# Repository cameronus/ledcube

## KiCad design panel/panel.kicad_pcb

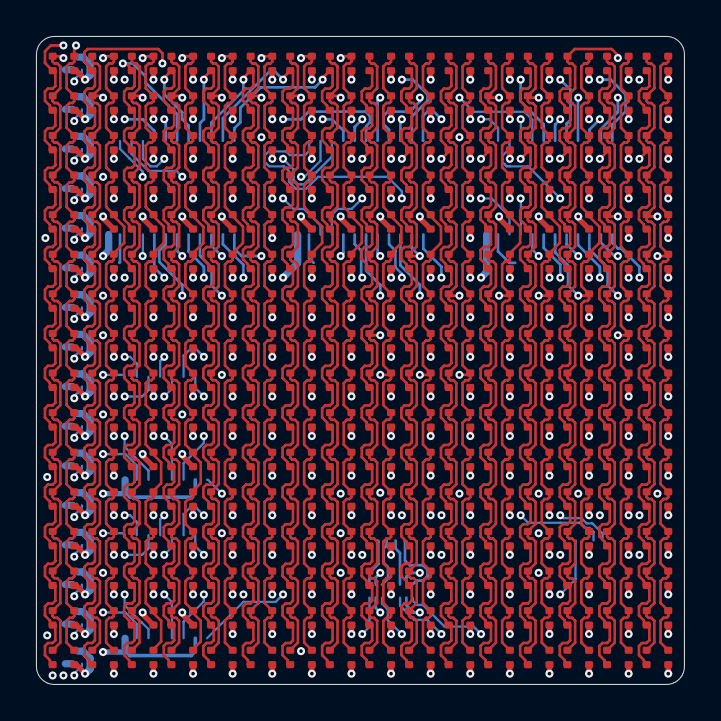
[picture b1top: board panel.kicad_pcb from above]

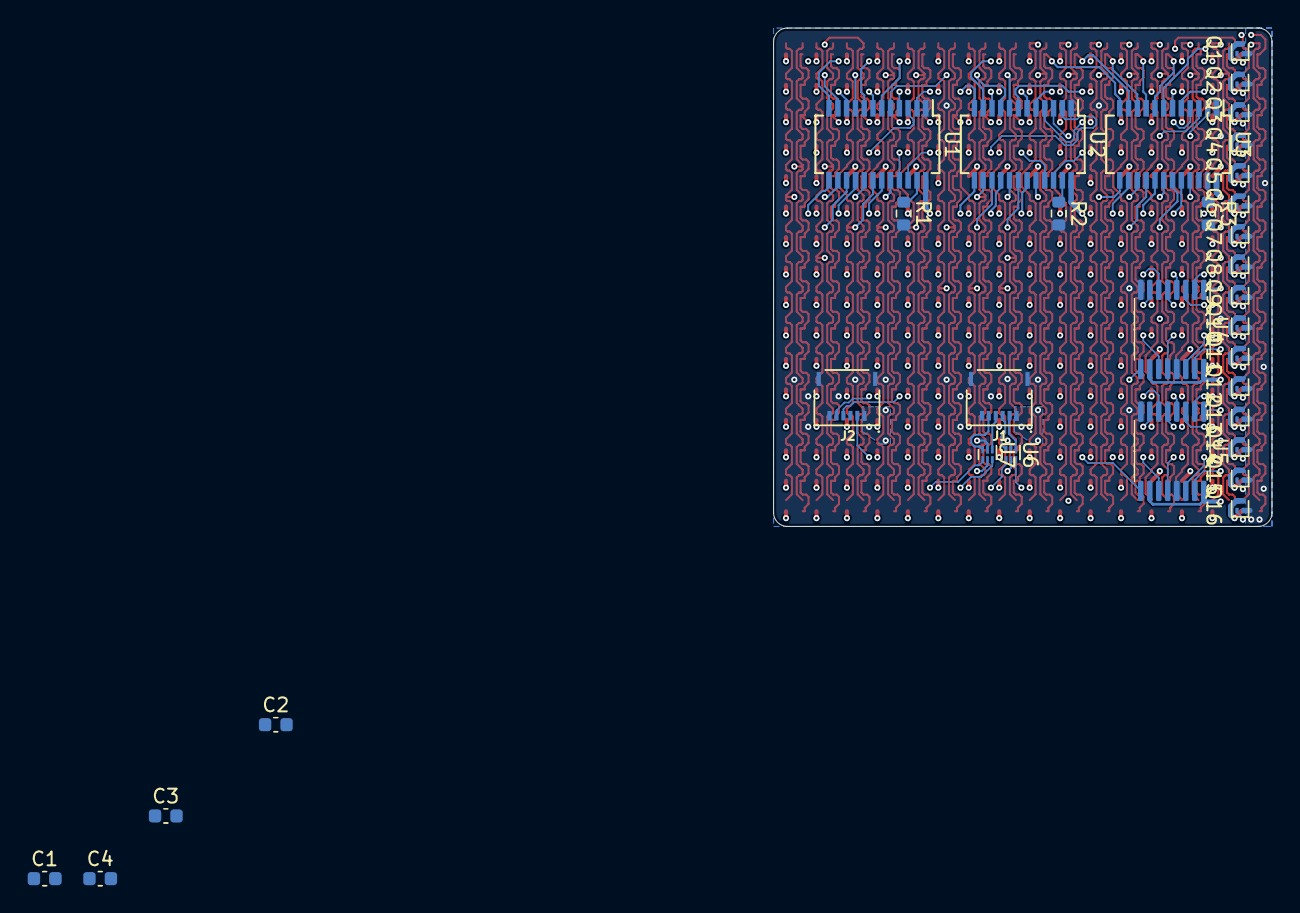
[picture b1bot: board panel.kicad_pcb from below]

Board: 4 copper layers, 36.0 x 36.0 mm, 288 parts (32 on the bottom side), 98 nets.

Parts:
C1, C2, C3, C4: 0.1uF; C_0603_1608Metric
D1, D2, D3, D4, D5, D6, D7, D8, D9, D10, D11, D12, D13, D14, D15, D16, D17, D18, D19, D20, D21, D22, D23, D24, D25, D26, D27, D28, D29, D30, D31, D32, D33, D34, D35, D36, D37, D38, D39, D40, D41, D42, D43, D44, D45, D46, D47, D48, D49, D50, D51, D52, D53, D54, D55, D56, D57, D58, D59, D60, D61, D62, D63, D64, D65, D66, D67, D68, D69, D70, D71, D72, D73, D74, D75, D76, D77, D78, D79, D80, D81, D82, D83, D84, D85, D86, D87, D88, D89, D90, D91, D92, D93, D94, D95, D96, D97, D98, D99, D100, D101, D102, D103, D104, D105, D106, D107, D108, D109, D110, D111, D112, D113, D114, D115, D116, D117, D118, D119, D120, D121, D122, D123, D124, D125, D126, D127, D128, D129, D130, D131, D132, D133, D134, D135, D136, D137, D138, D139, D140, D141, D142, D143, D144, D145, D146, D147, D148, D149, D150, D151, D152, D153, D154, D155, D156, D157, D158, D159, D160, D161, D162, D163, D164, D165, D166, D167, D168, D169, D170, D171, D172, D173, D174, D175, D176, D177, D178, D179, D180, D181, D182, D183, D184, D185, D186, D187, D188, D189, D190, D191, D192, D193, D194, D195, D196, D197, D198, D199, D200, D201, D202, D203, D204, D205, D206, D207, D208, D209, D210, D211, D212, D213, D214, D215, D216, D217, D218, D219, D220, D221, D222, D223, D224, D225, D226, D227, D228, D229, D230, D231, D232, D233, D234, D235, D236, D237, D238, D239, D240, D241, D242, D243, D244, D245, D246, D247, D248, D249, D250, D251, D252, D253, D254, D255, D256: LED_RABG; MHPA1515RGBDT
J1: IN; 5034800600
J2: OUT; 5034800600
Q1, Q2, Q3, Q4, Q5, Q6, Q7, Q8, Q9, Q10, Q11, Q12, Q13, Q14, Q15, Q16: Q_PMOS_GSD; SOT-883
R1: 2.2k; R_0603_1608Metric
R2: 7.5k; R_0603_1608Metric
R3: 4.12k; R_0603_1608Metric
U1, U2, U3: TLC59025; SSOP-24_3.9x8.7mm_P0.635mm
U4, U5: SN74HC595; TSSOP-16_4.4x5mm_P0.65mm
U6, U7: NC7WZ17; Fairchild_MicroPak2-6_1.0x1.0mm_P0.35mm

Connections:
/BLANK: J2.5, U1.21 (~OE), U2.21 (~OE), U3.21 (~OE), U7.4 (Y2)
/BLANK_IN: J1.5, U7.3 (A2)
/CLK: J2.2, U1.3 (CLK), U2.3 (CLK), U3.3 (CLK), U4.11 (SRCLK), U5.11 (SRCLK), U6.6 (Y1)
/CLK_IN: J1.2, U6.1 (A1)
/DAT: U4.14 (SER), U6.4 (Y2)
/DAT2: U4.9 (QH'), U5.14 (SER)
/DAT3: U1.2 (SDI), U5.9 (QH')
/DAT4: U1.22 (SDO), U2.2 (SDI)
/DAT5: U2.22 (SDO), U3.2 (SDI)
/DAT_IN: J1.3, U6.3 (A2)
/DAT_OUT: J2.3, U3.22 (SDO)
/LATCH: J2.4, U1.4 (LE), U2.4 (LE), U3.4 (LE), U4.12 (RCLK), U5.12 (RCLK), U7.6 (Y1)
/LATCH_IN: J1.4, U7.1 (A1)
/ROW_0: Q1.1 (G), U4.15 (QA)
/ROW_0/COMMON: D1.2 (A), D2.2 (A), D3.2 (A), D4.2 (A), D5.2 (A), D6.2 (A), D7.2 (A), D8.2 (A), D9.2 (A), D10.2 (A), D11.2 (A), D12.2 (A), D13.2 (A), D14.2 (A), D15.2 (A), D16.2 (A), Q1.3 (D)
/ROW_1: Q2.1 (G), U4.1 (QB)
/ROW_1/COMMON: D17.2 (A), D18.2 (A), D19.2 (A), D20.2 (A), D21.2 (A), D22.2 (A), D23.2 (A), D24.2 (A), D25.2 (A), D26.2 (A), D27.2 (A), D28.2 (A), D29.2 (A), D30.2 (A), D31.2 (A), D32.2 (A), Q2.3 (D)
/ROW_2: Q3.1 (G), U4.2 (QC)
/ROW_2/COMMON: D33.2 (A), D34.2 (A), D35.2 (A), D36.2 (A), D37.2 (A), D38.2 (A), D39.2 (A), D40.2 (A), D41.2 (A), D42.2 (A), D43.2 (A), D44.2 (A), D45.2 (A), D46.2 (A), D47.2 (A), D48.2 (A), Q3.3 (D)
/ROW_3: Q4.1 (G), U4.3 (QD)
/ROW_3/COMMON: D49.2 (A), D50.2 (A), D51.2 (A), D52.2 (A), D53.2 (A), D54.2 (A), D55.2 (A), D56.2 (A), D57.2 (A), D58.2 (A), D59.2 (A), D60.2 (A), D61.2 (A), D62.2 (A), D63.2 (A), D64.2 (A), Q4.3 (D)
/ROW_4: Q5.1 (G), U4.4 (QE)
/ROW_4/COMMON: D65.2 (A), D66.2 (A), D67.2 (A), D68.2 (A), D69.2 (A), D70.2 (A), D71.2 (A), D72.2 (A), D73.2 (A), D74.2 (A), D75.2 (A), D76.2 (A), D77.2 (A), D78.2 (A), D79.2 (A), D80.2 (A), Q5.3 (D)
/ROW_5: Q6.1 (G), U4.5 (QF)
/ROW_5/COMMON: D81.2 (A), D82.2 (A), D83.2 (A), D84.2 (A), D85.2 (A), D86.2 (A), D87.2 (A), D88.2 (A), D89.2 (A), D90.2 (A), D91.2 (A), D92.2 (A), D93.2 (A), D94.2 (A), D95.2 (A), D96.2 (A), Q6.3 (D)
/ROW_6: Q7.1 (G), U4.6 (QG)
/ROW_6/COMMON: D97.2 (A), D98.2 (A), D99.2 (A), D100.2 (A), D101.2 (A), D102.2 (A), D103.2 (A), D104.2 (A), D105.2 (A), D106.2 (A), D107.2 (A), D108.2 (A), D109.2 (A), D110.2 (A), D111.2 (A), D112.2 (A), Q7.3 (D)
/ROW_7: Q8.1 (G), U4.7 (QH)
/ROW_7/COMMON: D113.2 (A), D114.2 (A), D115.2 (A), D116.2 (A), D117.2 (A), D118.2 (A), D119.2 (A), D120.2 (A), D121.2 (A), D122.2 (A), D123.2 (A), D124.2 (A), D125.2 (A), D126.2 (A), D127.2 (A), D128.2 (A), Q8.3 (D)
/ROW_8: Q9.1 (G), U5.15 (QA)
/ROW_8/COMMON: D129.2 (A), D130.2 (A), D131.2 (A), D132.2 (A), D133.2 (A), D134.2 (A), D135.2 (A), D136.2 (A), D137.2 (A), D138.2 (A), D139.2 (A), D140.2 (A), D141.2 (A), D142.2 (A), D143.2 (A), D144.2 (A), Q9.3 (D)
/ROW_9: Q10.1 (G), U5.1 (QB)
/ROW_9/COMMON: D145.2 (A), D146.2 (A), D147.2 (A), D148.2 (A), D149.2 (A), D150.2 (A), D151.2 (A), D152.2 (A), D153.2 (A), D154.2 (A), D155.2 (A), D156.2 (A), D157.2 (A), D158.2 (A), D159.2 (A), D160.2 (A), Q10.3 (D)
/ROW_10: Q11.1 (G), U5.2 (QC)
/ROW_10/COMMON: D161.2 (A), D162.2 (A), D163.2 (A), D164.2 (A), D165.2 (A), D166.2 (A), D167.2 (A), D168.2 (A), D169.2 (A), D170.2 (A), D171.2 (A), D172.2 (A), D173.2 (A), D174.2 (A), D175.2 (A), D176.2 (A), Q11.3 (D)
/ROW_11: Q12.1 (G), U5.3 (QD)
/ROW_11/COMMON: D177.2 (A), D178.2 (A), D179.2 (A), D180.2 (A), D181.2 (A), D182.2 (A), D183.2 (A), D184.2 (A), D185.2 (A), D186.2 (A), D187.2 (A), D188.2 (A), D189.2 (A), D190.2 (A), D191.2 (A), D192.2 (A), Q12.3 (D)
/ROW_12: Q13.1 (G), U5.4 (QE)
/ROW_12/COMMON: D193.2 (A), D194.2 (A), D195.2 (A), D196.2 (A), D197.2 (A), D198.2 (A), D199.2 (A), D200.2 (A), D201.2 (A), D202.2 (A), D203.2 (A), D204.2 (A), D205.2 (A), D206.2 (A), D207.2 (A), D208.2 (A), Q13.3 (D)
/ROW_13: Q14.1 (G), U5.5 (QF)
/ROW_13/COMMON: D209.2 (A), D210.2 (A), D211.2 (A), D212.2 (A), D213.2 (A), D214.2 (A), D215.2 (A), D216.2 (A), D217.2 (A), D218.2 (A), D219.2 (A), D220.2 (A), D221.2 (A), D222.2 (A), D223.2 (A), D224.2 (A), Q14.3 (D)
/ROW_14: Q15.1 (G), U5.6 (QG)
/ROW_14/COMMON: D225.2 (A), D226.2 (A), D227.2 (A), D228.2 (A), D229.2 (A), D230.2 (A), D231.2 (A), D232.2 (A), D233.2 (A), D234.2 (A), D235.2 (A), D236.2 (A), D237.2 (A), D238.2 (A), D239.2 (A), D240.2 (A), Q15.3 (D)
/ROW_15: Q16.1 (G), U5.7 (QH)
/ROW_15/COMMON: D241.2 (A), D242.2 (A), D243.2 (A), D244.2 (A), D245.2 (A), D246.2 (A), D247.2 (A), D248.2 (A), D249.2 (A), D250.2 (A), D251.2 (A), D252.2 (A), D253.2 (A), D254.2 (A), D255.2 (A), D256.2 (A), Q16.3 (D)
COL_0B: D1.3 (BK), D17.3 (BK), D33.3 (BK), D49.3 (BK), D65.3 (BK), D81.3 (BK), D97.3 (BK), D113.3 (BK), D129.3 (BK), D145.3 (BK), D161.3 (BK), D177.3 (BK), D193.3 (BK), D209.3 (BK), D225.3 (BK), D241.3 (BK), U3.5 (~OUT0)
COL_0G: D1.4 (GK), D17.4 (GK), D33.4 (GK), D49.4 (GK), D65.4 (GK), D81.4 (GK), D97.4 (GK), D113.4 (GK), D129.4 (GK), D145.4 (GK), D161.4 (GK), D177.4 (GK), D193.4 (GK), D209.4 (GK), D225.4 (GK), D241.4 (GK), U2.5 (~OUT0)
COL_0R: D1.1 (RK), D17.1 (RK), D33.1 (RK), D49.1 (RK), D65.1 (RK), D81.1 (RK), D97.1 (RK), D113.1 (RK), D129.1 (RK), D145.1 (RK), D161.1 (RK), D177.1 (RK), D193.1 (RK), D209.1 (RK), D225.1 (RK), D241.1 (RK), U1.5 (~OUT0)
COL_1B: D2.3 (BK), D18.3 (BK), D34.3 (BK), D50.3 (BK), D66.3 (BK), D82.3 (BK), D98.3 (BK), D114.3 (BK), D130.3 (BK), D146.3 (BK), D162.3 (BK), D178.3 (BK), D194.3 (BK), D210.3 (BK), D226.3 (BK), D242.3 (BK), U3.6 (~OUT1)
COL_1G: D2.4 (GK), D18.4 (GK), D34.4 (GK), D50.4 (GK), D66.4 (GK), D82.4 (GK), D98.4 (GK), D114.4 (GK), D130.4 (GK), D146.4 (GK), D162.4 (GK), D178.4 (GK), D194.4 (GK), D210.4 (GK), D226.4 (GK), D242.4 (GK), U2.6 (~OUT1)
COL_1R: D2.1 (RK), D18.1 (RK), D34.1 (RK), D50.1 (RK), D66.1 (RK), D82.1 (RK), D98.1 (RK), D114.1 (RK), D130.1 (RK), D146.1 (RK), D162.1 (RK), D178.1 (RK), D194.1 (RK), D210.1 (RK), D226.1 (RK), D242.1 (RK), U1.6 (~OUT1)
COL_2B: D3.3 (BK), D19.3 (BK), D35.3 (BK), D51.3 (BK), D67.3 (BK), D83.3 (BK), D99.3 (BK), D115.3 (BK), D131.3 (BK), D147.3 (BK), D163.3 (BK), D179.3 (BK), D195.3 (BK), D211.3 (BK), D227.3 (BK), D243.3 (BK), U3.7 (~OUT2)
COL_2G: D3.4 (GK), D19.4 (GK), D35.4 (GK), D51.4 (GK), D67.4 (GK), D83.4 (GK), D99.4 (GK), D115.4 (GK), D131.4 (GK), D147.4 (GK), D163.4 (GK), D179.4 (GK), D195.4 (GK), D211.4 (GK), D227.4 (GK), D243.4 (GK), U2.7 (~OUT2)
COL_2R: D3.1 (RK), D19.1 (RK), D35.1 (RK), D51.1 (RK), D67.1 (RK), D83.1 (RK), D99.1 (RK), D115.1 (RK), D131.1 (RK), D147.1 (RK), D163.1 (RK), D179.1 (RK), D195.1 (RK), D211.1 (RK), D227.1 (RK), D243.1 (RK), U1.7 (~OUT2)
COL_3B: D4.3 (BK), D20.3 (BK), D36.3 (BK), D52.3 (BK), D68.3 (BK), D84.3 (BK), D100.3 (BK), D116.3 (BK), D132.3 (BK), D148.3 (BK), D164.3 (BK), D180.3 (BK), D196.3 (BK), D212.3 (BK), D228.3 (BK), D244.3 (BK), U3.8 (~OUT3)
COL_3G: D4.4 (GK), D20.4 (GK), D36.4 (GK), D52.4 (GK), D68.4 (GK), D84.4 (GK), D100.4 (GK), D116.4 (GK), D132.4 (GK), D148.4 (GK), D164.4 (GK), D180.4 (GK), D196.4 (GK), D212.4 (GK), D228.4 (GK), D244.4 (GK), U2.8 (~OUT3)
COL_3R: D4.1 (RK), D20.1 (RK), D36.1 (RK), D52.1 (RK), D68.1 (RK), D84.1 (RK), D100.1 (RK), D116.1 (RK), D132.1 (RK), D148.1 (RK), D164.1 (RK), D180.1 (RK), D196.1 (RK), D212.1 (RK), D228.1 (RK), D244.1 (RK), U1.8 (~OUT3)
COL_4B: D5.3 (BK), D21.3 (BK), D37.3 (BK), D53.3 (BK), D69.3 (BK), D85.3 (BK), D101.3 (BK), D117.3 (BK), D133.3 (BK), D149.3 (BK), D165.3 (BK), D181.3 (BK), D197.3 (BK), D213.3 (BK), D229.3 (BK), D245.3 (BK), U3.9 (~OUT4)
COL_4G: D5.4 (GK), D21.4 (GK), D37.4 (GK), D53.4 (GK), D69.4 (GK), D85.4 (GK), D101.4 (GK), D117.4 (GK), D133.4 (GK), D149.4 (GK), D165.4 (GK), D181.4 (GK), D197.4 (GK), D213.4 (GK), D229.4 (GK), D245.4 (GK), U2.9 (~OUT4)
COL_4R: D5.1 (RK), D21.1 (RK), D37.1 (RK), D53.1 (RK), D69.1 (RK), D85.1 (RK), D101.1 (RK), D117.1 (RK), D133.1 (RK), D149.1 (RK), D165.1 (RK), D181.1 (RK), D197.1 (RK), D213.1 (RK), D229.1 (RK), D245.1 (RK), U1.9 (~OUT4)
COL_5B: D6.3 (BK), D22.3 (BK), D38.3 (BK), D54.3 (BK), D70.3 (BK), D86.3 (BK), D102.3 (BK), D118.3 (BK), D134.3 (BK), D150.3 (BK), D166.3 (BK), D182.3 (BK), D198.3 (BK), D214.3 (BK), D230.3 (BK), D246.3 (BK), U3.10 (~OUT5)
COL_5G: D6.4 (GK), D22.4 (GK), D38.4 (GK), D54.4 (GK), D70.4 (GK), D86.4 (GK), D102.4 (GK), D118.4 (GK), D134.4 (GK), D150.4 (GK), D166.4 (GK), D182.4 (GK), D198.4 (GK), D214.4 (GK), D230.4 (GK), D246.4 (GK), U2.10 (~OUT5)
COL_5R: D6.1 (RK), D22.1 (RK), D38.1 (RK), D54.1 (RK), D70.1 (RK), D86.1 (RK), D102.1 (RK), D118.1 (RK), D134.1 (RK), D150.1 (RK), D166.1 (RK), D182.1 (RK), D198.1 (RK), D214.1 (RK), D230.1 (RK), D246.1 (RK), U1.10 (~OUT5)
COL_6B: D7.3 (BK), D23.3 (BK), D39.3 (BK), D55.3 (BK), D71.3 (BK), D87.3 (BK), D103.3 (BK), D119.3 (BK), D135.3 (BK), D151.3 (BK), D167.3 (BK), D183.3 (BK), D199.3 (BK), D215.3 (BK), D231.3 (BK), D247.3 (BK), U3.11 (~OUT6)
COL_6G: D7.4 (GK), D23.4 (GK), D39.4 (GK), D55.4 (GK), D71.4 (GK), D87.4 (GK), D103.4 (GK), D119.4 (GK), D135.4 (GK), D151.4 (GK), D167.4 (GK), D183.4 (GK), D199.4 (GK), D215.4 (GK), D231.4 (GK), D247.4 (GK), U2.11 (~OUT6)
COL_6R: D7.1 (RK), D23.1 (RK), D39.1 (RK), D55.1 (RK), D71.1 (RK), D87.1 (RK), D103.1 (RK), D119.1 (RK), D135.1 (RK), D151.1 (RK), D167.1 (RK), D183.1 (RK), D199.1 (RK), D215.1 (RK), D231.1 (RK), D247.1 (RK), U1.11 (~OUT6)
COL_7B: D8.3 (BK), D24.3 (BK), D40.3 (BK), D56.3 (BK), D72.3 (BK), D88.3 (BK), D104.3 (BK), D120.3 (BK), D136.3 (BK), D152.3 (BK), D168.3 (BK), D184.3 (BK), D200.3 (BK), D216.3 (BK), D232.3 (BK), D248.3 (BK), U3.12 (~OUT7)
COL_7G: D8.4 (GK), D24.4 (GK), D40.4 (GK), D56.4 (GK), D72.4 (GK), D88.4 (GK), D104.4 (GK), D120.4 (GK), D136.4 (GK), D152.4 (GK), D168.4 (GK), D184.4 (GK), D200.4 (GK), D216.4 (GK), D232.4 (GK), D248.4 (GK), U2.12 (~OUT7)
COL_7R: D8.1 (RK), D24.1 (RK), D40.1 (RK), D56.1 (RK), D72.1 (RK), D88.1 (RK), D104.1 (RK), D120.1 (RK), D136.1 (RK), D152.1 (RK), D168.1 (RK), D184.1 (RK), D200.1 (RK), D216.1 (RK), D232.1 (RK), D248.1 (RK), U1.12 (~OUT7)
COL_8B: D9.3 (BK), D25.3 (BK), D41.3 (BK), D57.3 (BK), D73.3 (BK), D89.3 (BK), D105.3 (BK), D121.3 (BK), D137.3 (BK), D153.3 (BK), D169.3 (BK), D185.3 (BK), D201.3 (BK), D217.3 (BK), D233.3 (BK), D249.3 (BK), U3.13 (~OUT8)
COL_8G: D9.4 (GK), D25.4 (GK), D41.4 (GK), D57.4 (GK), D73.4 (GK), D89.4 (GK), D105.4 (GK), D121.4 (GK), D137.4 (GK), D153.4 (GK), D169.4 (GK), D185.4 (GK), D201.4 (GK), D217.4 (GK), D233.4 (GK), D249.4 (GK), U2.13 (~OUT8)
COL_8R: D9.1 (RK), D25.1 (RK), D41.1 (RK), D57.1 (RK), D73.1 (RK), D89.1 (RK), D105.1 (RK), D121.1 (RK), D137.1 (RK), D153.1 (RK), D169.1 (RK), D185.1 (RK), D201.1 (RK), D217.1 (RK), D233.1 (RK), D249.1 (RK), U1.13 (~OUT8)
COL_9B: D10.3 (BK), D26.3 (BK), D42.3 (BK), D58.3 (BK), D74.3 (BK), D90.3 (BK), D106.3 (BK), D122.3 (BK), D138.3 (BK), D154.3 (BK), D170.3 (BK), D186.3 (BK), D202.3 (BK), D218.3 (BK), D234.3 (BK), D250.3 (BK), U3.14 (~OUT9)
COL_9G: D10.4 (GK), D26.4 (GK), D42.4 (GK), D58.4 (GK), D74.4 (GK), D90.4 (GK), D106.4 (GK), D122.4 (GK), D138.4 (GK), D154.4 (GK), D170.4 (GK), D186.4 (GK), D202.4 (GK), D218.4 (GK), D234.4 (GK), D250.4 (GK), U2.14 (~OUT9)
COL_9R: D10.1 (RK), D26.1 (RK), D42.1 (RK), D58.1 (RK), D74.1 (RK), D90.1 (RK), D106.1 (RK), D122.1 (RK), D138.1 (RK), D154.1 (RK), D170.1 (RK), D186.1 (RK), D202.1 (RK), D218.1 (RK), D234.1 (RK), D250.1 (RK), U1.14 (~OUT9)
COL_10B: D11.3 (BK), D27.3 (BK), D43.3 (BK), D59.3 (BK), D75.3 (BK), D91.3 (BK), D107.3 (BK), D123.3 (BK), D139.3 (BK), D155.3 (BK), D171.3 (BK), D187.3 (BK), D203.3 (BK), D219.3 (BK), D235.3 (BK), D251.3 (BK), U3.15 (~OUT10)
COL_10G: D11.4 (GK), D27.4 (GK), D43.4 (GK), D59.4 (GK), D75.4 (GK), D91.4 (GK), D107.4 (GK), D123.4 (GK), D139.4 (GK), D155.4 (GK), D171.4 (GK), D187.4 (GK), D203.4 (GK), D219.4 (GK), D235.4 (GK), D251.4 (GK), U2.15 (~OUT10)
COL_10R: D11.1 (RK), D27.1 (RK), D43.1 (RK), D59.1 (RK), D75.1 (RK), D91.1 (RK), D107.1 (RK), D123.1 (RK), D139.1 (RK), D155.1 (RK), D171.1 (RK), D187.1 (RK), D203.1 (RK), D219.1 (RK), D235.1 (RK), D251.1 (RK), U1.15 (~OUT10)
COL_11B: D12.3 (BK), D28.3 (BK), D44.3 (BK), D60.3 (BK), D76.3 (BK), D92.3 (BK), D108.3 (BK), D124.3 (BK), D140.3 (BK), D156.3 (BK), D172.3 (BK), D188.3 (BK), D204.3 (BK), D220.3 (BK), D236.3 (BK), D252.3 (BK), U3.16 (~OUT11)
COL_11G: D12.4 (GK), D28.4 (GK), D44.4 (GK), D60.4 (GK), D76.4 (GK), D92.4 (GK), D108.4 (GK), D124.4 (GK), D140.4 (GK), D156.4 (GK), D172.4 (GK), D188.4 (GK), D204.4 (GK), D220.4 (GK), D236.4 (GK), D252.4 (GK), U2.16 (~OUT11)
COL_11R: D12.1 (RK), D28.1 (RK), D44.1 (RK), D60.1 (RK), D76.1 (RK), D92.1 (RK), D108.1 (RK), D124.1 (RK), D140.1 (RK), D156.1 (RK), D172.1 (RK), D188.1 (RK), D204.1 (RK), D220.1 (RK), D236.1 (RK), D252.1 (RK), U1.16 (~OUT11)
COL_12B: D13.3 (BK), D29.3 (BK), D45.3 (BK), D61.3 (BK), D77.3 (BK), D93.3 (BK), D109.3 (BK), D125.3 (BK), D141.3 (BK), D157.3 (BK), D173.3 (BK), D189.3 (BK), D205.3 (BK), D221.3 (BK), D237.3 (BK), D253.3 (BK), U3.17 (~OUT12)
COL_12G: D13.4 (GK), D29.4 (GK), D45.4 (GK), D61.4 (GK), D77.4 (GK), D93.4 (GK), D109.4 (GK), D125.4 (GK), D141.4 (GK), D157.4 (GK), D173.4 (GK), D189.4 (GK), D205.4 (GK), D221.4 (GK), D237.4 (GK), D253.4 (GK), U2.17 (~OUT12)
COL_12R: D13.1 (RK), D29.1 (RK), D45.1 (RK), D61.1 (RK), D77.1 (RK), D93.1 (RK), D109.1 (RK), D125.1 (RK), D141.1 (RK), D157.1 (RK), D173.1 (RK), D189.1 (RK), D205.1 (RK), D221.1 (RK), D237.1 (RK), D253.1 (RK), U1.17 (~OUT12)
COL_13B: D14.3 (BK), D30.3 (BK), D46.3 (BK), D62.3 (BK), D78.3 (BK), D94.3 (BK), D110.3 (BK), D126.3 (BK), D142.3 (BK), D158.3 (BK), D174.3 (BK), D190.3 (BK), D206.3 (BK), D222.3 (BK), D238.3 (BK), D254.3 (BK), U3.18 (~OUT13)
COL_13G: D14.4 (GK), D30.4 (GK), D46.4 (GK), D62.4 (GK), D78.4 (GK), D94.4 (GK), D110.4 (GK), D126.4 (GK), D142.4 (GK), D158.4 (GK), D174.4 (GK), D190.4 (GK), D206.4 (GK), D222.4 (GK), D238.4 (GK), D254.4 (GK), U2.18 (~OUT13)
COL_13R: D14.1 (RK), D30.1 (RK), D46.1 (RK), D62.1 (RK), D78.1 (RK), D94.1 (RK), D110.1 (RK), D126.1 (RK), D142.1 (RK), D158.1 (RK), D174.1 (RK), D190.1 (RK), D206.1 (RK), D222.1 (RK), D238.1 (RK), D254.1 (RK), U1.18 (~OUT13)
COL_14B: D15.3 (BK), D31.3 (BK), D47.3 (BK), D63.3 (BK), D79.3 (BK), D95.3 (BK), D111.3 (BK), D127.3 (BK), D143.3 (BK), D159.3 (BK), D175.3 (BK), D191.3 (BK), D207.3 (BK), D223.3 (BK), D239.3 (BK), D255.3 (BK), U3.19 (~OUT14)
COL_14G: D15.4 (GK), D31.4 (GK), D47.4 (GK), D63.4 (GK), D79.4 (GK), D95.4 (GK), D111.4 (GK), D127.4 (GK), D143.4 (GK), D159.4 (GK), D175.4 (GK), D191.4 (GK), D207.4 (GK), D223.4 (GK), D239.4 (GK), D255.4 (GK), U2.19 (~OUT14)
COL_14R: D15.1 (RK), D31.1 (RK), D47.1 (RK), D63.1 (RK), D79.1 (RK), D95.1 (RK), D111.1 (RK), D127.1 (RK), D143.1 (RK), D159.1 (RK), D175.1 (RK), D191.1 (RK), D207.1 (RK), D223.1 (RK), D239.1 (RK), D255.1 (RK), U1.19 (~OUT14)
COL_15B: D16.3 (BK), D32.3 (BK), D48.3 (BK), D64.3 (BK), D80.3 (BK), D96.3 (BK), D112.3 (BK), D128.3 (BK), D144.3 (BK), D160.3 (BK), D176.3 (BK), D192.3 (BK), D208.3 (BK), D224.3 (BK), D240.3 (BK), D256.3 (BK), U3.20 (~OUT15)
COL_15G: D16.4 (GK), D32.4 (GK), D48.4 (GK), D64.4 (GK), D80.4 (GK), D96.4 (GK), D112.4 (GK), D128.4 (GK), D144.4 (GK), D160.4 (GK), D176.4 (GK), D192.4 (GK), D208.4 (GK), D224.4 (GK), D240.4 (GK), D256.4 (GK), U2.20 (~OUT15)
COL_15R: D16.1 (RK), D32.1 (RK), D48.1 (RK), D64.1 (RK), D80.1 (RK), D96.1 (RK), D112.1 (RK), D128.1 (RK), D144.1 (RK), D160.1 (RK), D176.1 (RK), D192.1 (RK), D208.1 (RK), D224.1 (RK), D240.1 (RK), D256.1 (RK), U1.20 (~OUT15)
GND: C1.2, C2.2, C3.2, C4.2, J1.6, J1.SH (Shield), J2.6, J2.SH (Shield), R1.2, R2.2, R3.2, U1.1 (GND), U2.1 (GND), U3.1 (GND), U4.8 (GND), U4.13 (~OE), U5.8 (GND), U5.13 (~OE), U6.2 (GND), U7.2 (GND)
unnamed: R1.1, U1.23 (REXT)
unnamed: R2.1, U2.23 (REXT)
unnamed: R3.1, U3.23 (REXT)
VCC: C1.1, C2.1, C3.1, C4.1, J1.1, J2.1, Q1.2 (S), Q2.2 (S), Q3.2 (S), Q4.2 (S), Q5.2 (S), Q6.2 (S), Q7.2 (S), Q8.2 (S), Q9.2 (S), Q10.2 (S), Q11.2 (S), Q12.2 (S), Q13.2 (S), Q14.2 (S), Q15.2 (S), Q16.2 (S), U1.24 (VDD), U2.24 (VDD), U3.24 (VDD), U4.10 (~SRCLR), U4.16 (VCC), U5.10 (~SRCLR), U5.16 (VCC), U6.5 (VCC), U7.5 (VCC)

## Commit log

2021-07-19 LED driver/shift register symbol, hierarchical row sheet
2021-07-20 Row/column labels attached to shift registers/drivers
2021-07-21 PMOS drivers, buffers, and serial connections
2021-07-21 Connectors and decoupling caps
2021-07-21 LED footprint
2021-07-21 Moving panel to subfolder
2021-07-21 Annotated schematic
2021-07-22 LED matrix placement
2021-07-22 Routed columns
2021-07-22 Routed rows
2021-07-22 Modified column routing
2021-07-22 Routing fixes and CC drivers placed
2021-07-23 Placed row driver MOSFETs
2021-07-23 VCC plane and row driver placement
2021-07-23 Routed rows around row driver pins
2021-07-24 First option for row MOSFET layout
2021-07-24 New strategy for powering rows
2021-07-24 Row gates 0-7 routed
2021-07-25 Rerouted first half of row drivers
2021-07-25 Routed second half of row drivers
2021-07-26 Routed first 8 columns of blue and green channels
2021-07-26 Modified copper pours
2021-07-26 Columns 0-7 of R/G/B channels fully routed
2021-07-26 Routed columns 7-15 of blue channel
2021-07-26 Routed columns 7-15 of green channel
2021-07-26 Routed all R/G/B columns
2021-07-27 Working on routing serial signals
2021-07-28 More signal routing
2021-07-28 Placed connectors and routed buffers
2021-07-28 Routed all data signals
2021-07-28 Placed decoupling caps
2021-07-28 Finished routing and adding ground vias
2021-07-29 Silkscreen cleanup
2021-07-29 More touchups
2021-07-30 Shrunk board width
2021-08-08 Silkscreen art and production files
2021-11-28 Breakout PCB
